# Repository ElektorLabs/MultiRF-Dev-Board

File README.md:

# MultiRF-Dev-Board
MultiRF Dev Board

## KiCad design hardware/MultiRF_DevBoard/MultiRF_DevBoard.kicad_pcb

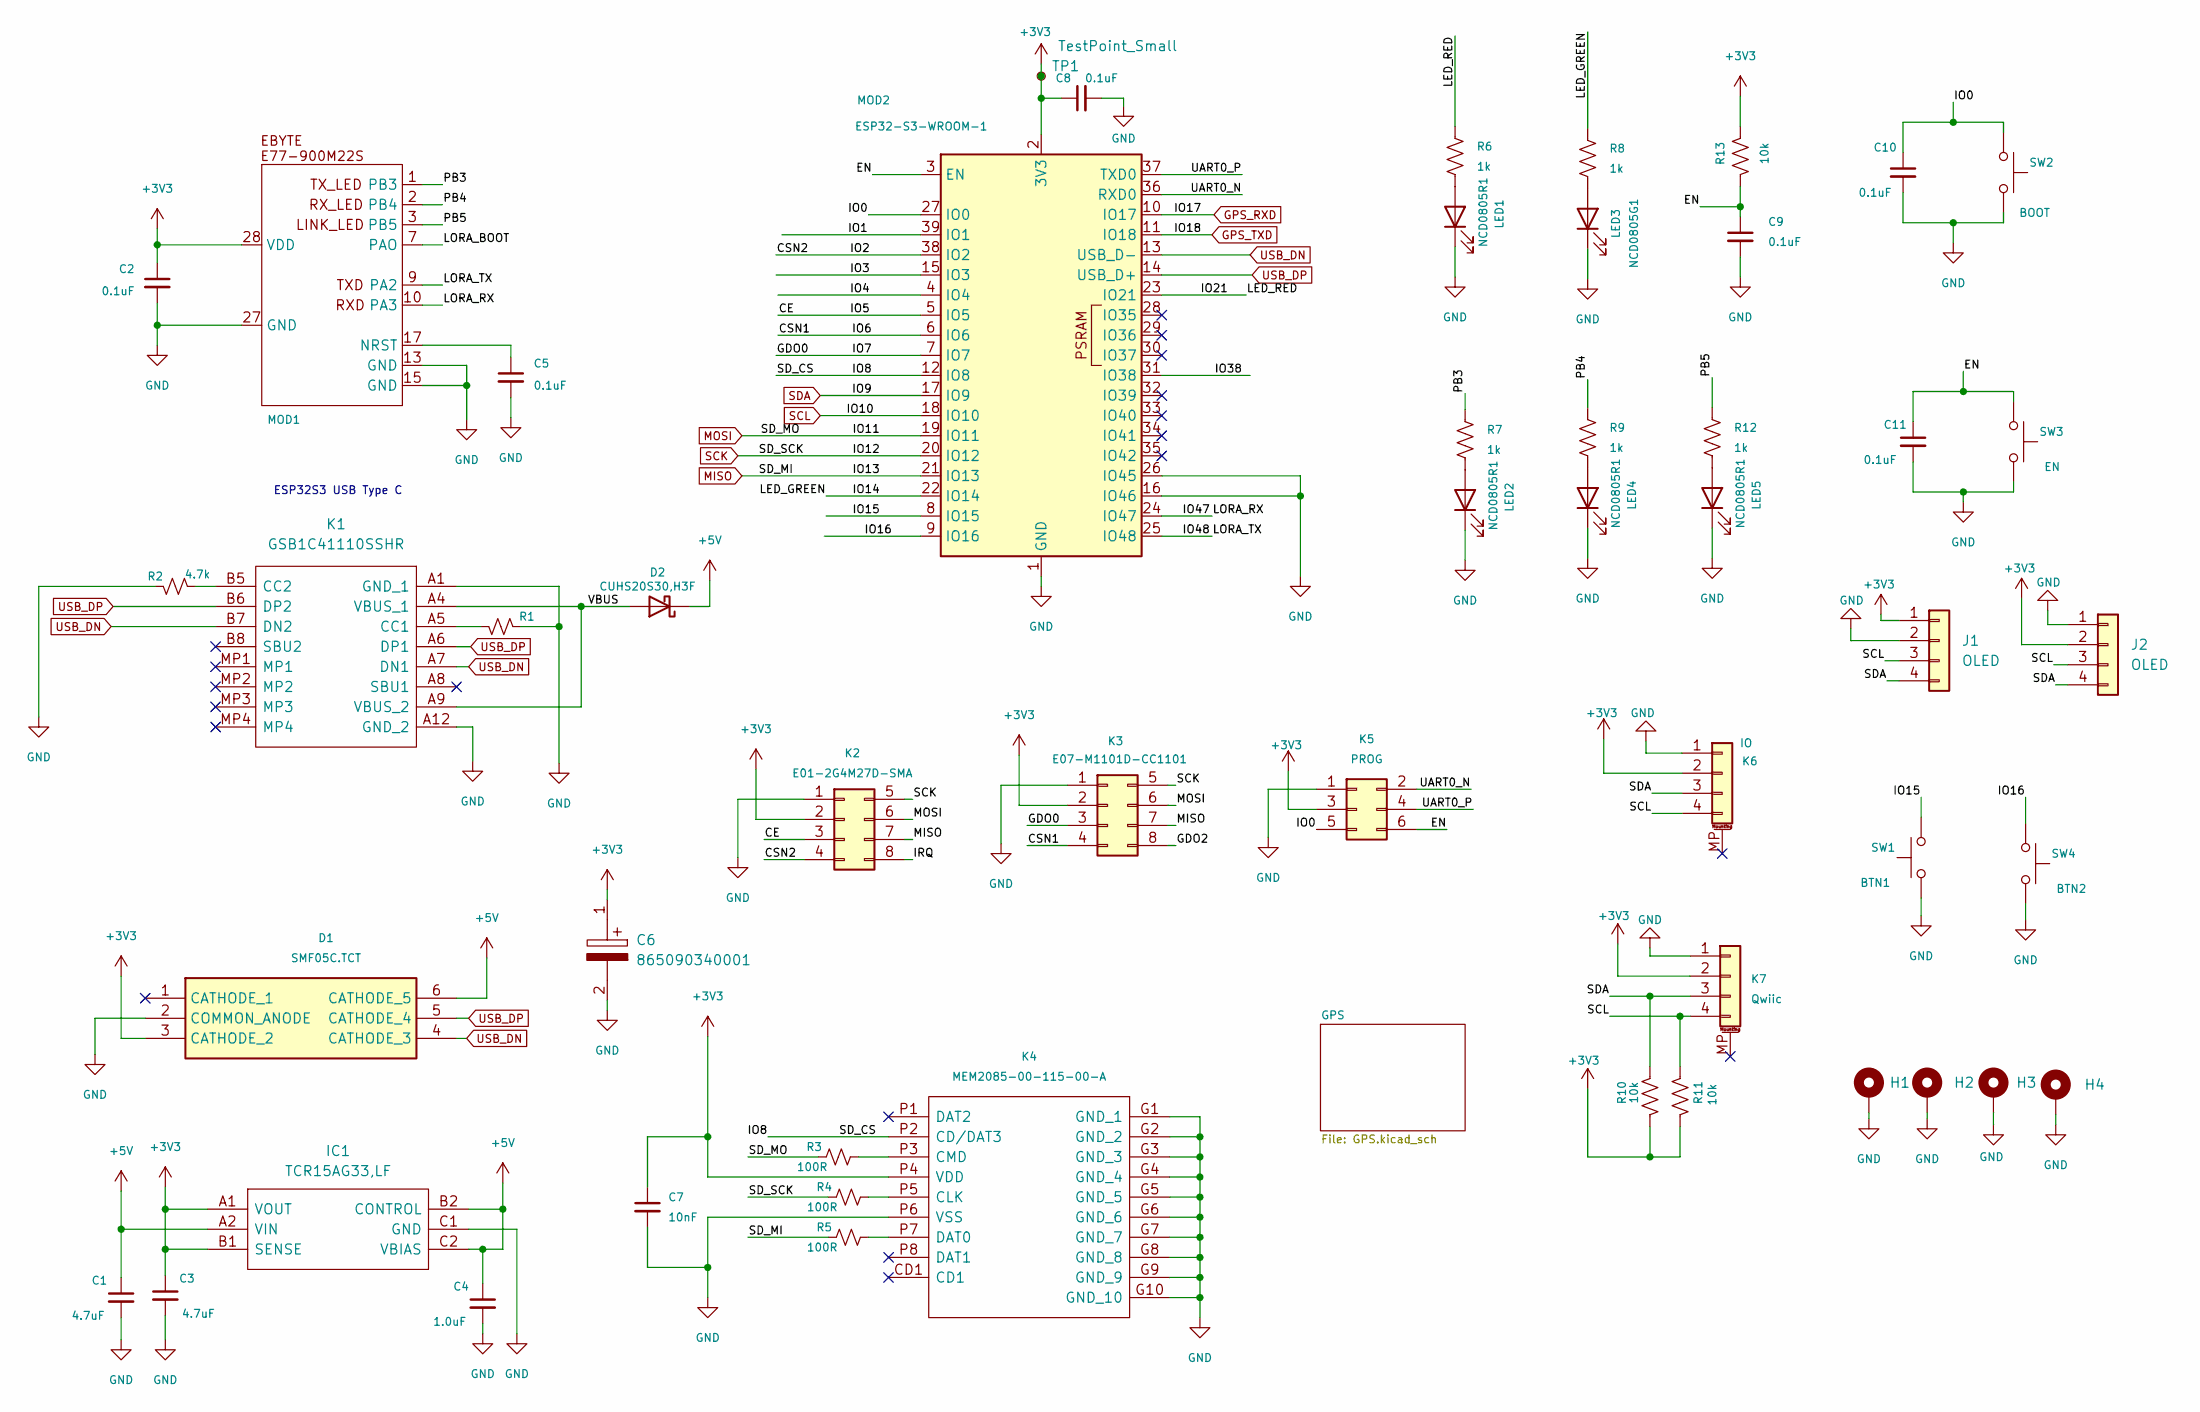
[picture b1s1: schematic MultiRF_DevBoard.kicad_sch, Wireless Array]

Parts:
C1, C3: 4.7uF; C_0805_2012Metric; Manufacturer_Part_Number C0805C104M5RACTU; Mouser Part Number 80-C0805C104M5R
C2, C5, C10, C11: 0.1uF; C_0805_2012Metric; Manufacturer_Part_Number C0805C104M5RACTU; Mouser Part Number 80-C0805C104M5R
C4: 1.0uF; C_0805_2012Metric; Manufacturer_Part_Number C0805C104M5RACTU; Mouser Part Number 80-C0805C104M5R
C6: 865090340001; CAPAE430X550N; Mouser Part Number 710-865090340001
C7: 10nF; C_0805_2012Metric; Manufacturer_Part_Number C0402C103K5RAC7411; Mouser Part Number 80-C0402C103K5R7411
C8, C9: 0.1uF; C_0805_2012Metric; Manufacturer_Part_Number C1608X7R1H104K080AA; Mouser Part Number 810-C1608X7R1H104K
D1: SMF05C.TCT; SOT65P210X110-6N; Mouser Part Number 947-SMF05C.TCT
D2: CUHS20S30,H3F; CUHS20S40H3F; Mouser Part Number 757-CUHS20S30H3F
H1, H2, H3, H4: MountingHole_Pad; MountingHole_3.2mm_M3_DIN965_Pad
IC1: TCR15AG33,LF; BGA6C40P2X3_80X120X33; Mouser Part Number 757-TCR15AG33LF
J1, J2: OLED; PinHeader_1x04_P2.54mm_Vertical
K1: GSB1C41110SSHR; Manufacturer_Part_Number GSB1C41110SSHR
K2: E01-2G4M27D-SMA; PinHeader_2x04_P2.54mm_Vertical
K3: E07-M1101D-CC1101; PinHeader_2x04_P2.54mm_Vertical
K4: MEM2085-00-115-00-A; MEM20850011500A; Mouser Part Number 640-MEM20850011500A
K5: PROG; PinHeader_2x03_P2.54mm_Vertical; Manufacturer_Part_Number PinHeader_2x03_P2.54mm_Vertical
K6: IO; JST_PH_S4B-PH-SM4-TB_1x04-1MP_P2.00mm_Horizontal; Manufacturer_Part_Number JST_PH_S4B-PH-SM4-TB_1x04-1MP_P2.00mm_H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
K7: Qwiic; JST_SH_SM04B-SRSS-TB_1x04-1MP_P1.00mm_Horizontal; Manufacturer_Part_Number JST_SH_SM04B-SRSS-TB_1x04-1MP_P1.00mm_H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
LED1, LED2, LED4, LED5: NCD0805R1; LED_0805_2012Metric_Pad1.15x1.40mm_HandSolder; Manufacturer_Part_Number NCD0805R1
LED3: NCD0805G1; LED_0805_2012Metric_Pad1.15x1.40mm_HandSolder; Manufacturer_Part_Number NCD0805G1
MOD1: E07-900M10S
MOD2: ESP32-S3-WROOM-1; Manufacturer_Part_Number ESP32-S3-WROOM-1
R1, R2: 4.7k; R_0805_2012Metric; Manufacturer_Part_Number RCS06034K70FKEA; Mouser Part Number 71-RCS06034K70FKEA
R3, R4, R5: 100R; R_0805_2012Metric; Manufacturer_Part_Number MCT0603PD1000DP500; Mouser Part Number 594-MCT0603PD1000DP5
R6, R7, R8, R9, R12: 1k; R_0805_2012Metric; Manufacturer_Part_Number CHP0805-FX-1001ELF; Mouser Part Number 652-CHP0805FX1001ELF
R10, R11, R13: 10k; R_0805_2012Metric; Manufacturer_Part_Number RCS060310K0FKEA; Mouser Part Number 71-RCS060310K0JNEA
SW1: BTN1; SKRKAEE020; Manufacturer_Part_Number SKRKAEE020; Mouser Part Number SKRKAEE020
SW2: BOOT; SKRKAEE020; Manufacturer_Part_Number SKRKAEE020; Mouser Part Number SKRKAEE020
SW3: EN; SKRKAEE020; Manufacturer_Part_Number SKRKAEE020; Mouser Part Number SKRKAEE020
SW4: BTN2; SKRKAEE020; Manufacturer_Part_Number SKRKAEE020; Mouser Part Number SKRKAEE020
TP1: TestPoint_Small

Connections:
+3V3: C2.1, C3.1, C6.1, C7.1, C8.1, D1.3 (CATHODE_2), IC1.A1 (VOUT), IC1.B1 (SENSE), J1.1, J2.2, K2.2, K3.2, K4.P4 (VDD), K5.3, K6.2, K7.2, MOD1.28 (VDD), MOD2.2 (3V3), R10.1, R11.1, R13.2, TP1.1; also elsewhere on the board
+5V: C1.1, C4.1, D1.6 (CATHODE_5), D2.1 (K), IC1.A2 (VIN), IC1.B2 (CONTROL), IC1.C2 (VBIAS)
/CE: K2.3, MOD2.5 (IO5)
/CSN1: K3.4, MOD2.6 (IO6)
/CSN2: K2.4, MOD2.38 (IO2)
/EN: C9.1, C11.1, K5.6, MOD2.3 (EN), R13.1, SW3.1
/GDO0: K3.3, MOD2.7 (IO7)
/GDO2: K3.8
/IO0: C10.1, K5.5, MOD2.27 (IO0), SW2.1
/IO1: MOD2.39 (IO1)
/IO3: MOD2.15 (IO3)
/IO4: MOD2.4 (IO4)
/IO8: K4.P2 (CD/DAT3), MOD2.12 (IO8)
/IO14: MOD2.22 (IO14), R8.2
/IO15: MOD2.8 (IO15), SW1.1
/IO16: MOD2.9 (IO16), SW4.1
/IO21: MOD2.23 (IO21), R6.2
/IO38: MOD2.31 (IO38)
/IO47: MOD1.10 (PA3), MOD2.24 (IO47)
/IO48: MOD1.9 (PA2), MOD2.25 (IO48)
/IRQ: K2.8
/LORA_BOOT: MOD1.7 (PAO)
/PB3: MOD1.1 (PB3), R7.2
/PB4: MOD1.2 (PB4), R9.2
/PB5: MOD1.3 (PB5), R12.2
/UART0_N: K5.2, MOD2.36 (RXD0)
/UART0_P: K5.4, MOD2.37 (TXD0)
/VBUS: D2.2 (A), K1.A4 (VBUS_1), K1.A9 (VBUS_2)
GND: C1.2, C2.2, C3.2, C4.2, C5.2, C6.2, C7.2, C8.2, C9.2, C10.2, C11.2, D1.2 (COMMON_ANODE), H1.1 (1_1), H2.1 (1_1), H3.1 (1_1), H4.1 (1_1), IC1.C1 (GND), J1.2, J2.1, K1.A1 (GND_1), K1.A12 (GND_2), K2.1, K3.1, K4.G1 (GND_1), K4.G2 (GND_2), K4.G3 (GND_3), K4.G4 (GND_4), K4.G5 (GND_5), K4.G6 (GND_6), K4.G7 (GND_7), K4.G8 (GND_8), K4.G9 (GND_9), K4.G10 (GND_10), K4.P6 (VSS), K5.1, K6.1, K7.1, LED1.1 (K), LED2.1 (K), LED3.1 (K), LED4.1 (K), LED5.1 (K), MOD1.13 (GND), MOD1.15 (GND), MOD1.27 (GND), MOD2.1 (GND), MOD2.16 (IO46), MOD2.26 (IO45), MOD2.40 (GND), MOD2.41 (GND), R1.2, R2.1, SW1.2, SW2.2, SW3.2, SW4.2; also elsewhere on the board
GPS_RXD: MOD2.10 (IO17); also elsewhere on the board
GPS_TXD: MOD2.11 (IO18); also elsewhere on the board
MISO: K2.7, K3.7, MOD2.21 (IO13), R5.1
MOSI: K2.6, K3.6, MOD2.19 (IO11), R3.1
unnamed: K1.A5 (CC1), R1.1
unnamed: K1.B5 (CC2), R2.2
unnamed: K4.P5 (CLK), R4.2
unnamed: K4.P3 (CMD), R3.2
unnamed: K4.P7 (DAT0), R5.2
unnamed: LED1.2 (A), R6.1
unnamed: LED2.2 (A), R7.1
unnamed: LED3.2 (A), R8.1
unnamed: LED4.2 (A), R9.1
unnamed: LED5.2 (A), R12.1
unnamed: C5.1, MOD1.17 (NRST)
SCK: K2.5, K3.5, MOD2.20 (IO12), R4.1
SCL: J1.3, J2.3, K6.4, K7.4, MOD2.18 (IO10), R11.2
SDA: J1.4, J2.4, K6.3, K7.3, MOD2.17 (IO9), R10.2
USB_DN: D1.4 (CATHODE_3), K1.A7 (DN1), K1.B7 (DN2), MOD2.13 (USB_D-)
USB_DP: D1.5 (CATHODE_4), K1.A6 (DP1), K1.B6 (DP2), MOD2.14 (USB_D+)

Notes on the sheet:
ESP32S3 USB Type C

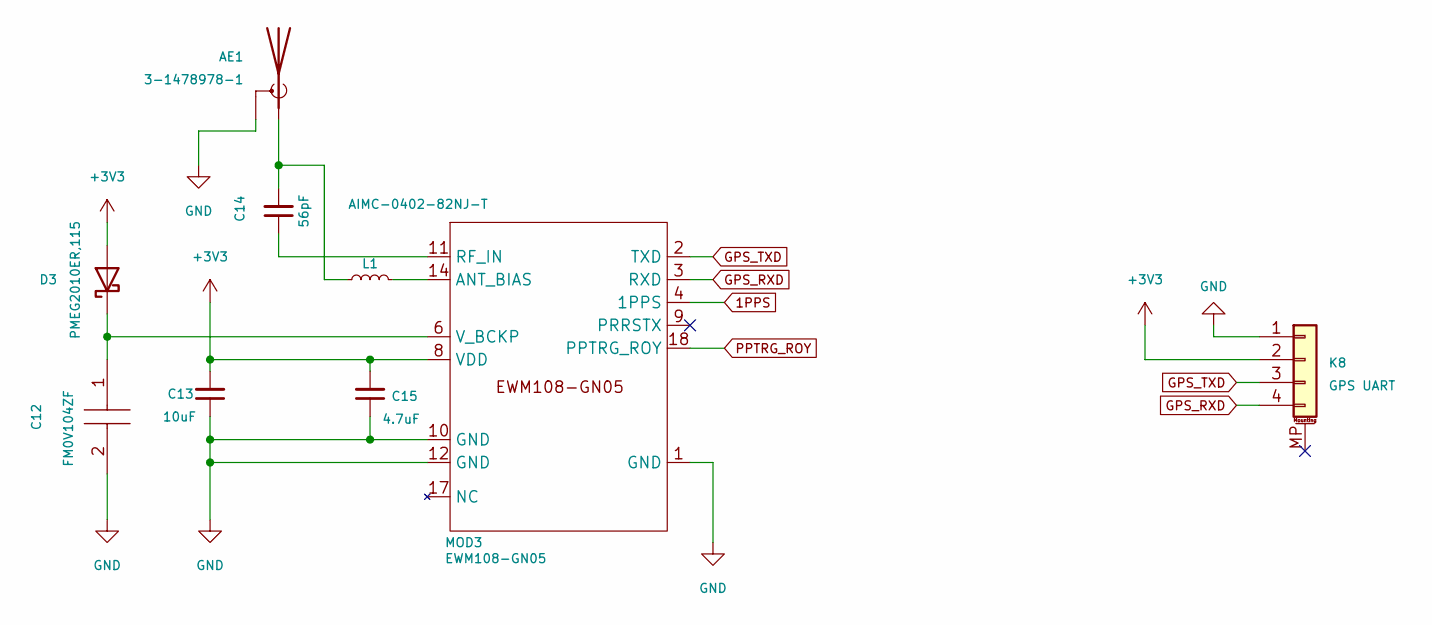
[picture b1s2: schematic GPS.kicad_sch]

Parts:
AE1: 3-1478978-1; 314789781; Mouser Part Number 571-3-1478978-1
C12: FM0V104ZF; Mouser Part Number 80-FM0V104ZF
C13: 10uF; C_0805_2012Metric; Mouser Part Number 81-GRM155R60J475ME7D
C14: 56pF; C_0603_1608Metric_Pad1.08x0.95mm_HandSolder; Manufacturer_Part_Number 600S560KT250T; Mouser Part Number 581-600S560KT250T
C15: 4.7uF; C_0805_2012Metric; Mouser Part Number 81-GRM155R60J475ME7D
D3: PMEG2010ER,115; PMEG2010ER115; Mouser Part Number 771-PMEG2010ER115
K8: GPS UART; JST_PH_S4B-PH-SM4-TB_1x04-1MP_P2.00mm_Horizontal; Manufacturer_Part_Number Connector_JST:JST_PH_S4B-PH-SM4-TB_1x04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
L1: AIMC-0402-82NJ-T; INDC1005X65N; Manufacturer_Part_Number AIMC-0402-82NJ-T
MOD3: EWM108-GN05; PCBComponent_1; Manufacturer_Part_Number EWM108-GN05

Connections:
1PPS: MOD3.4 (1PPS)
+3V3: C13.2, C15.2, D3.2 (A), K8.2, MOD3.8 (VDD); also elsewhere on the board
GND: AE1.1 (eShield), AE1.2 (Shield), AE1.3 (Shield), AE1.4 (Shield), C12.2, C13.1, C15.1, K8.1, MOD3.1 (GND), MOD3.10 (GND), MOD3.12 (GND); also elsewhere on the board
GPS_RXD: K8.4, MOD3.3 (RXD); also elsewhere on the board
GPS_TXD: K8.3, MOD3.2 (TXD); also elsewhere on the board
unnamed: AE1.5 (A), C14.2, L1.1
unnamed: C12.1, D3.1 (K), MOD3.6 (V_BCKP)
unnamed: L1.2, MOD3.14 (ANT_BIAS)
unnamed: C14.1, MOD3.11 (RF_IN)
PPTRG_ROY: MOD3.18 (PPTRG_ROY)

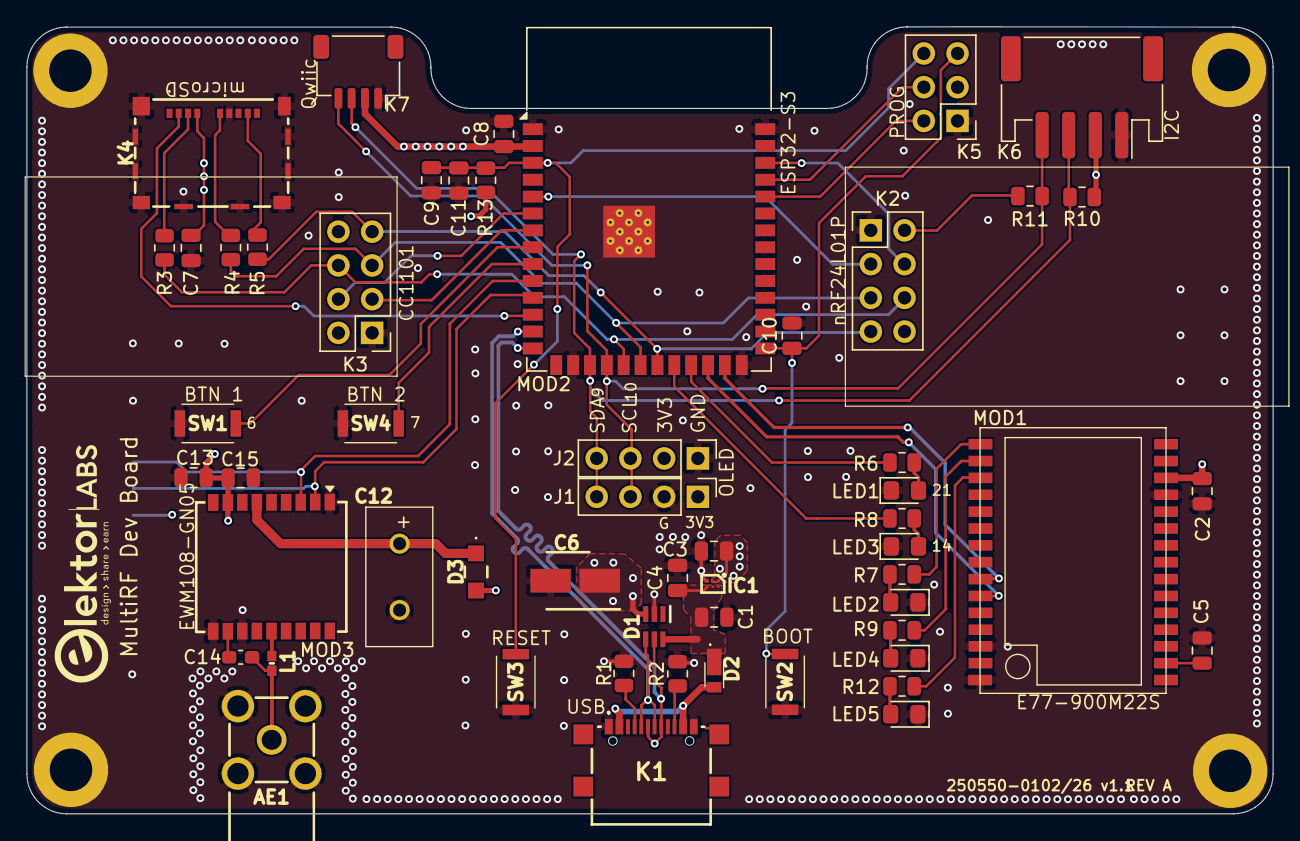
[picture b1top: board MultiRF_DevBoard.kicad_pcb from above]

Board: 4 copper layers, 93.8 x 59.3 mm, 60 parts (1 on the bottom side), 46 nets.
